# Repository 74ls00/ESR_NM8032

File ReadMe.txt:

Особенности варианта.

Конденсаторы полимерные LowESR с материнской платы.

Преобразователь с 3в до 6в.
Установлена 34063 потомучто их много. При питании ниже 2.6в у ней пропадает стабилизация и снижается напряжение с повышением пульсаций, поэтому выходное около 7.5в. Далее стабилизатор 78L06 снижает до стабильных 6в.
Дроссель (L3) после 34063 обязательный для снижения пульсаций микросхемы.
Использованы элементы LR03 из за доступности. Не рекомендуется для 34063 из за их низкого напряжения. Желательно литиевый аккумулятор 3.7в. Тогда можно попробывать убрать 78L06, и перестроить преобразователь на 6в.

DA3 LM3915N работает в режиме точки, для этоко вывод 9 никуда не подключен. Для режима шкалы мощность 78L06 слишком мала.

LM3915N разрабатывалась когда ток светодиодов был больше, возможно поэтому не учтена постоянная засветка первого светодиода. Для уменьшения нулевого тока через светодиод, он закорочен через резистор R28* 2k7, сопротивление подбирается под конкретный светодиод.

Прибор NM8032 для проверки ESR электролитических конденсаторов
https://masterkit.ru/blog/articles/pribor-nm8032-dlya-proverki-esr-elektroliticheskikh-kondensatorov

https://masterkit.ru/zip/nm8032.pdf
MD5: 05FAEDD55A1C5005F3642D41380A7DFE

Об измерении ESR и доработке NM8032
https://www.sites.google.com/a/lvsystem.ru/lab/praktika/measurement/esr-meter

Обсуждение этого варианта
Собрал пробник NM8032 для проверки ESR
https://radiokot.ru/forum/viewtopic.php?f=22&t=39489&start=20

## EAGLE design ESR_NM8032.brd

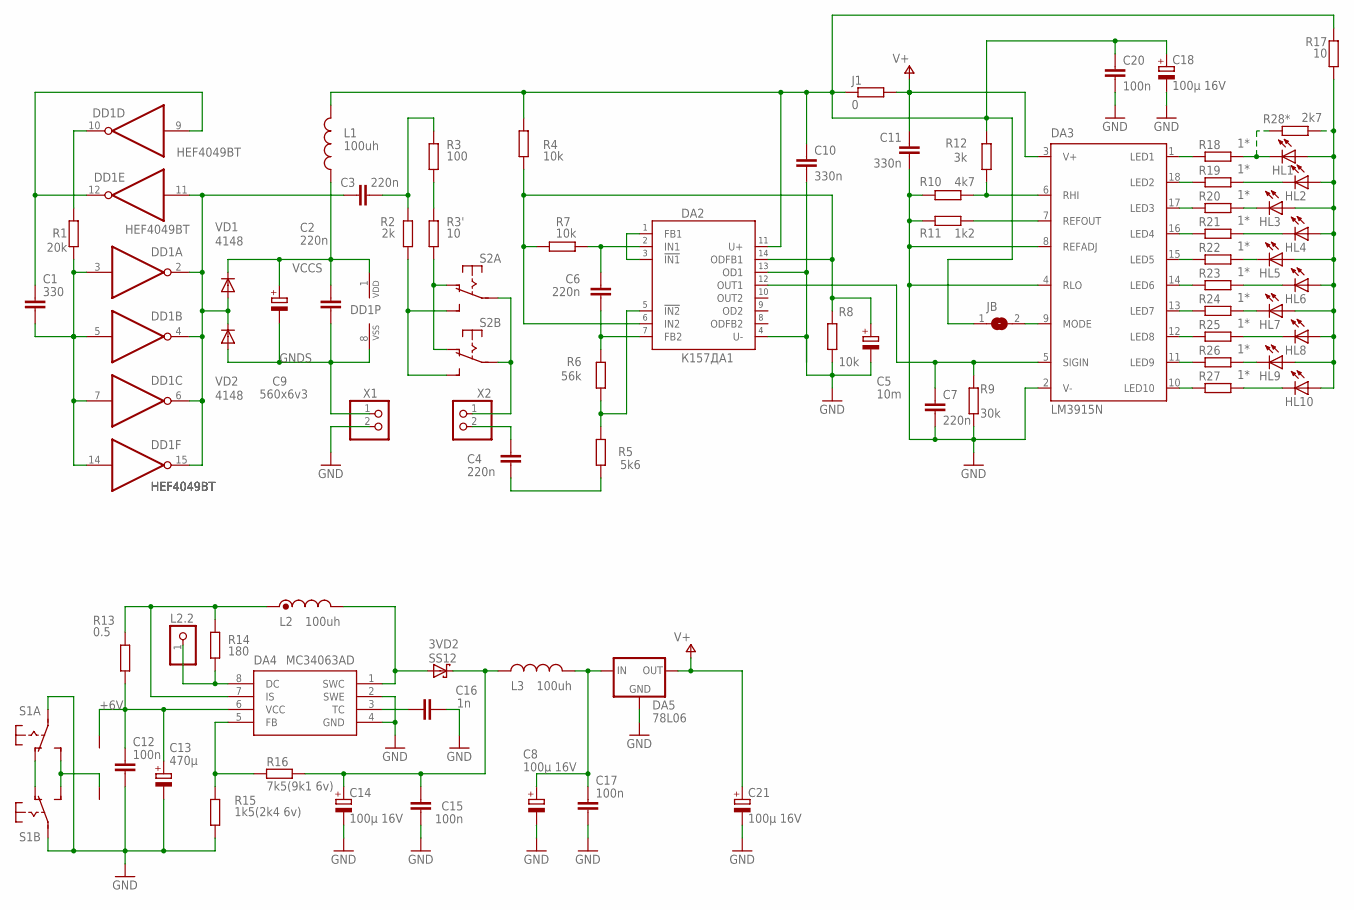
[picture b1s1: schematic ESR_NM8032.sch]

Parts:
3VD2: SS12; SMB
C1: 330; C0805
C2, C6: 220n; C075-032X103
C3, C4, C7: 220n; C0805
C5: 10m; E2-5
C8, C14, C18, C21: 100µ 16V; RCL_E2,5-5
C9: 560x6v3; HWPROGUSB_RCL_E3,5-8
C10, C11: 330n; C0805
C12, C15, C17, C20: 100n; C0805
C13: 470µ; RCL_E2,5-7
C16: 1n; C0805
DA2: К157ДА1; DIL14
DA3: LM3915N; DIL18
DA4: MC34063AD; SOIC8
DA5: 78L06; SOT89R
DD1: HEF4049BT; SO16
HL1, HL2, HL3, HL4, HL5, HL6, HL7, HL8, HL9, HL10: LED3MM
J1: 0; R1206W
JB: SJ
L1, L3: 100uh; 0207/10
L2: 100uh; 0204/7
L2.2: PINHD-1X1; 1X01
R1: 20k; M0805
R2: 2k; M0805
R3: 100; M0805
R3': 10; M0805
R4, R7, R8: 10k; R0805
R5: 5k6; M0805
R6: 56k; R0805
R9: 30k; R0805
R10: 4k7; R0805
R11: 1k2; R0805
R12: 3k; R0805
R13: 0.5; M1206
R14: 180; M0805
R15: 1k5(2k4 6v); M0805
R16: 7k5(9k1 6v); M0805
R17: 10; R0805
R18, R19, R20, R21, R22, R23, R24, R25, R26, R27: 1*; R0805
R28*: 2k7; R0805
S1, S2: SWITCH9X4
U$2: B-
U$4: B+
VD1, VD2: 4148; SOD80C
X1, X2: PINHD-1X2/2; 1X02

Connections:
+6V: C12.1, C13.+, DA4.6 (VCC), R13.1, U$4.P$1
GND: C5.-, C7.2, C8.-, C10.2, C11.2, C12.2, C13.-, C14.-, C15.1, C16.2, C17.2, C18.-, C20.2, C21.-, DA2.4 (U-), DA2.13 (OD1), DA3.2 (V-), DA3.4 (RLO), DA3.8 (REFADJ), DA4.2 (SWE), DA4.4 (GND), DA5.3 (GND), DA5.4 (GND), R8.1, R9.1, R10.1, R11.1, R15.1, S1.10, S1.20, X1.2
GNDS: C2.2, C9.-, DD1.8 (VSS), VD2.A, X1.1
unnamed: C1.2, DD1.3 (I), DD1.5 (I), DD1.7 (I), DD1.14 (I), R1.1
unnamed: C3.1, DD1.2 (O), DD1.4 (O), DD1.6 (O), DD1.11 (I), DD1.15 (O), VD1.A, VD2.C
unnamed: HL1.K (C), R18.2, R28*.1
unnamed: C1.1, DD1.9 (I), DD1.12 (O)
unnamed: HL2.K (C), R19.2
unnamed: DD1.10 (O), R1.2
unnamed: HL3.K (C), R20.2
unnamed: HL4.K (C), R21.2
unnamed: HL5.K (C), R22.2
unnamed: HL6.K (C), R23.2
unnamed: HL7.K (C), R24.2
unnamed: HL8.K (C), R25.2
unnamed: HL9.K (C), R26.2
unnamed: HL10.K (C), R27.2
unnamed: S2.10, S2.20, X2.1
unnamed: R3.1, R3'.2
unnamed: DA2.1 (FB1), DA2.3 (!IN1)
unnamed: C4.1, X2.2
unnamed: DA3.7 (REFOUT), R11.2
unnamed: DA3.6 (RHI), R10.2, R12.1
unnamed: C4.2, R5.1
unnamed: S1.12 (S), S1.22 (S), U$2.P$1
unnamed: C7.1, DA2.12 (OUT1), DA3.5 (SIGIN), R9.2
unnamed: S1.11 (O), S1.21 (O)
unnamed: C3.2, R2.2, R3.2
unnamed: DA3.1 (LED1), R18.1
unnamed: HL1.A, HL2.A, HL3.A, HL4.A, HL5.A, HL6.A, HL7.A, HL8.A, HL9.A, HL10.A, R17.2, R28*.2
unnamed: DA2.5 (!IN2), R5.2, R6.1
unnamed: DA4.8 (DC), L2.2.1, R14.1
unnamed: DA4.7 (IS), L2.1, R13.2, R14.2
unnamed: DA4.5 (FB), R15.2, R16.1
unnamed: 3VD2.A, DA4.1 (SWC), L2.2
unnamed: C16.1, DA4.3 (TC)
unnamed: C6.1, DA2.2 (IN1), R7.2
unnamed: C6.2, DA2.7 (FB2), R6.2
unnamed: C5.+, DA2.6 (IN2), DA2.14 (ODFB1), R4.1, R7.1, R8.2
unnamed: 3VD2.C, C14.+, C15.2, L3.1, R16.2
unnamed: DA3.18 (LED2), R19.1
unnamed: R3'.1, S2.11 (O), S2.21 (O)
unnamed: C10.1, C18.+, C20.1, DA2.11 (U+), J1.1, JB.1, L1.2, R4.2, R12.2, R17.1
unnamed: R2.1, S2.12 (S), S2.22 (S)
unnamed: DA3.17 (LED3), R20.1
unnamed: DA3.16 (LED4), R21.1
unnamed: DA3.15 (LED5), R22.1
unnamed: DA3.14 (LED6), R23.1
unnamed: DA3.13 (LED7), R24.1
unnamed: DA3.12 (LED8), R25.1
unnamed: DA3.11 (LED9), R26.1
unnamed: DA3.10 (LED10), R27.1
unnamed: DA3.9 (MODE), JB.2
unnamed: C8.+, C17.1, DA5.1 (IN), L3.2
V+: C11.1, C21.+, DA3.3 (V+), DA5.2 (OUT), J1.2
VCCS: C2.1, C9.+, DD1.1 (VDD), L1.1, VD1.C

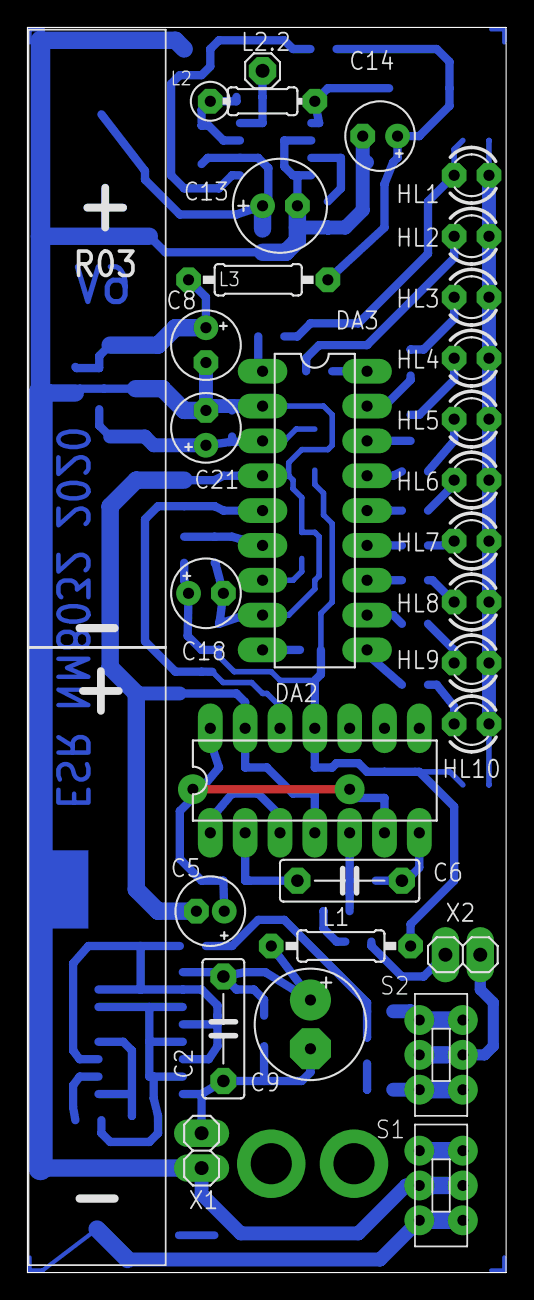
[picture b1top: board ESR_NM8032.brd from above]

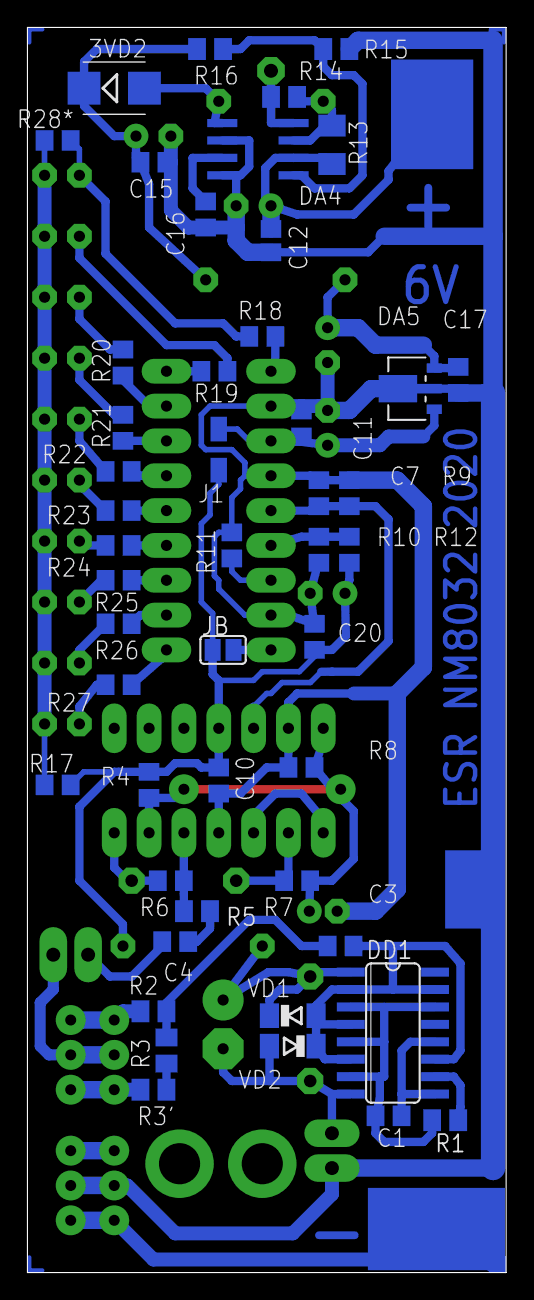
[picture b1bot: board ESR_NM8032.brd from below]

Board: 2 copper layers, 34.9 x 90.8 mm, 81 parts (50 on the bottom side), 56 nets.

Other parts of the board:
U$1, U$3: LR03

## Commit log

2019-08-04 pcspl
2020-07-19 new sch pdf
2020-07-25 sch fix
